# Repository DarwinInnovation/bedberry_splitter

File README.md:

# bedberry_splitter
Allows OKIN electric beds to be controlled from 2 handsets (and BedBerry v1)

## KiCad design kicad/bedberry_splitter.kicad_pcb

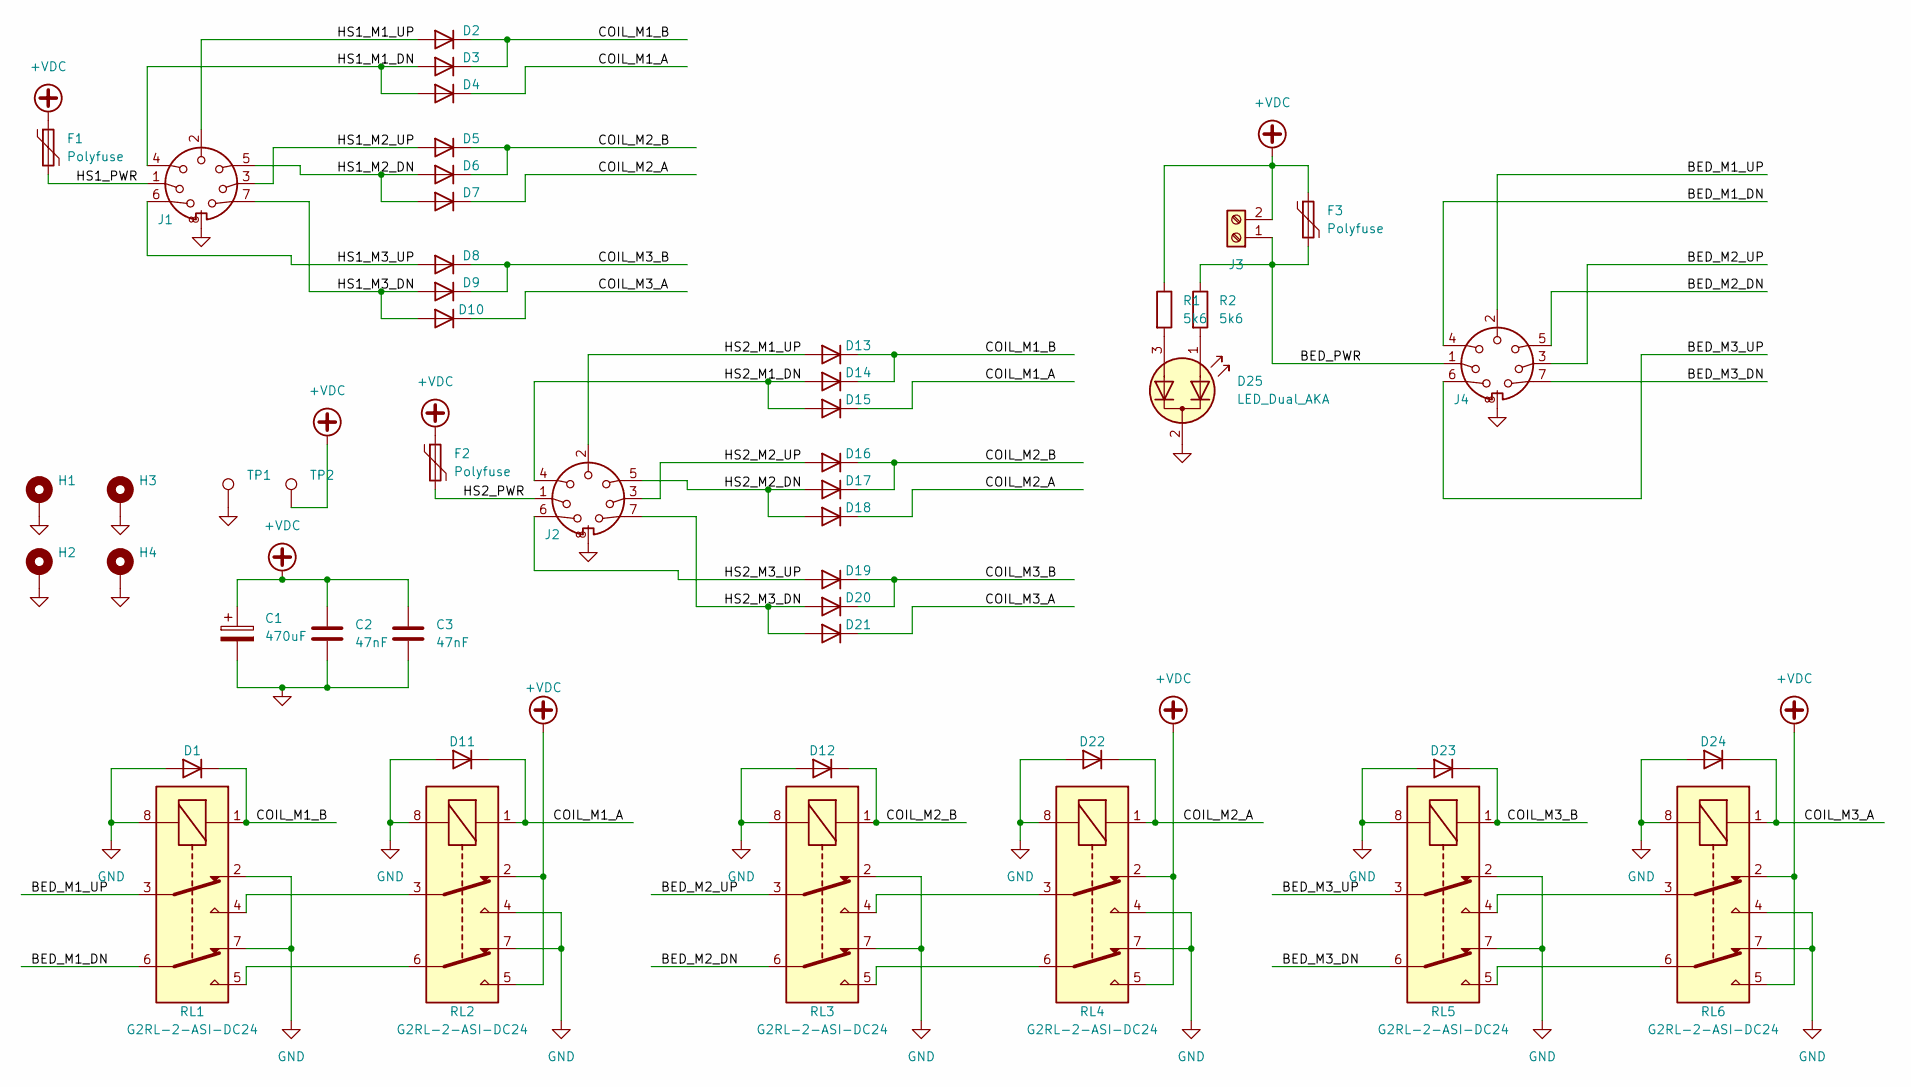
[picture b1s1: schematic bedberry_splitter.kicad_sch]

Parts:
C1: 470uF; CP_Radial_D10.0mm_P2.50mm_P5.00mm
C2, C3: 47nF; C_Disc_D7.5mm_W2.5mm_P5.00mm
D1, D2, D3, D4, D5, D6, D7, D8, D9, D10, D11, D12, D13, D14, D15, D16, D17, D18, D19, D20, D21, D22, D23, D24: 1N4002; D_DO-34_SOD68_P7.62mm_Horizontal
D25: LED_Dual_AKA; LED_D3.0mm-3
F1, F2, F3: Polyfuse; Fuse_Bourns_MF-RG300
H1, H2, H3, H4: MountingHole_Pad; MountingHole_2.7mm_M2.5_Pad
J1, J2, J4: DIN-7_with_Shield; pro-signal_DIN7_Socket
J3: Screw_Terminal_01x02; JST_NV_B02P-NV_1x02_P5.00mm_Vertical
R1, R2: 5k6; R_Axial_DIN0207_L6.3mm_D2.5mm_P2.54mm_Vertical
RL1, RL2, RL3, RL4, RL5, RL6: G2RL-2-ASI-DC24; Relay_DPDT_Omron_G2RL
TP1, TP2: TestPoint; TestPoint_Keystone_5005-5009_Compact

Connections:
+VDC: C1.1, C2.1, C3.1, F1.1, F2.1, F3.1, J3.2, R1.1, RL2.2, RL2.5, RL4.2, RL4.5, RL6.2, RL6.5, TP2.1
/BED_M1_DN: J4.4, RL1.6
/BED_M1_UP: J4.2, RL1.3
/BED_M2_DN: J4.5, RL3.6
/BED_M2_UP: J4.3, RL3.3
/BED_M3_DN: J4.7, RL5.6
/BED_M3_UP: J4.6, RL5.3
/BED_PWR: F3.2, J3.1, J4.1, R2.1
/COIL_M1_A: D4.1 (K), D11.1 (K), D15.1 (K), RL2.1
/COIL_M1_B: D1.1 (K), D2.1 (K), D3.1 (K), D13.1 (K), D14.1 (K), RL1.1
/COIL_M2_A: D7.1 (K), D18.1 (K), D22.1 (K), RL4.1
/COIL_M2_B: D5.1 (K), D6.1 (K), D12.1 (K), D16.1 (K), D17.1 (K), RL3.1
/COIL_M3_A: D10.1 (K), D21.1 (K), D24.1 (K), RL6.1
/COIL_M3_B: D8.1 (K), D9.1 (K), D19.1 (K), D20.1 (K), D23.1 (K), RL5.1
/HS1_M1_DN: D3.2 (A), D4.2 (A), J1.4
/HS1_M1_UP: D2.2 (A), J1.2
/HS1_M2_DN: D6.2 (A), D7.2 (A), J1.5
/HS1_M2_UP: D5.2 (A), J1.3
/HS1_M3_DN: D9.2 (A), D10.2 (A), J1.7
/HS1_M3_UP: D8.2 (A), J1.6
/HS1_PWR: F1.2, J1.1
/HS2_M1_DN: D14.2 (A), D15.2 (A), J2.4
/HS2_M1_UP: D13.2 (A), J2.2
/HS2_M2_DN: D17.2 (A), D18.2 (A), J2.5
/HS2_M2_UP: D16.2 (A), J2.3
/HS2_M3_DN: D20.2 (A), D21.2 (A), J2.7
/HS2_M3_UP: D19.2 (A), J2.6
/HS2_PWR: F2.2, J2.1
GND: C1.2, C2.2, C3.2, D1.2 (A), D11.2 (A), D12.2 (A), D22.2 (A), D23.2 (A), D24.2 (A), D25.2 (K), H1.1, H2.1, H3.1, H4.1, J1.8, J2.8, J4.8, RL1.2, RL1.7, RL1.8, RL2.4, RL2.7, RL2.8, RL3.2, RL3.7, RL3.8, RL4.4, RL4.7, RL4.8, RL5.2, RL5.7, RL5.8, RL6.4, RL6.7, RL6.8, TP1.1; also elsewhere on the board
unnamed: D25.1 (A1), R2.2
unnamed: D25.3 (A2), R1.2
unnamed: RL1.4, RL2.3
unnamed: RL1.5, RL2.6
unnamed: RL3.4, RL4.3
unnamed: RL3.5, RL4.6
unnamed: RL5.4, RL6.3
unnamed: RL5.5, RL6.6

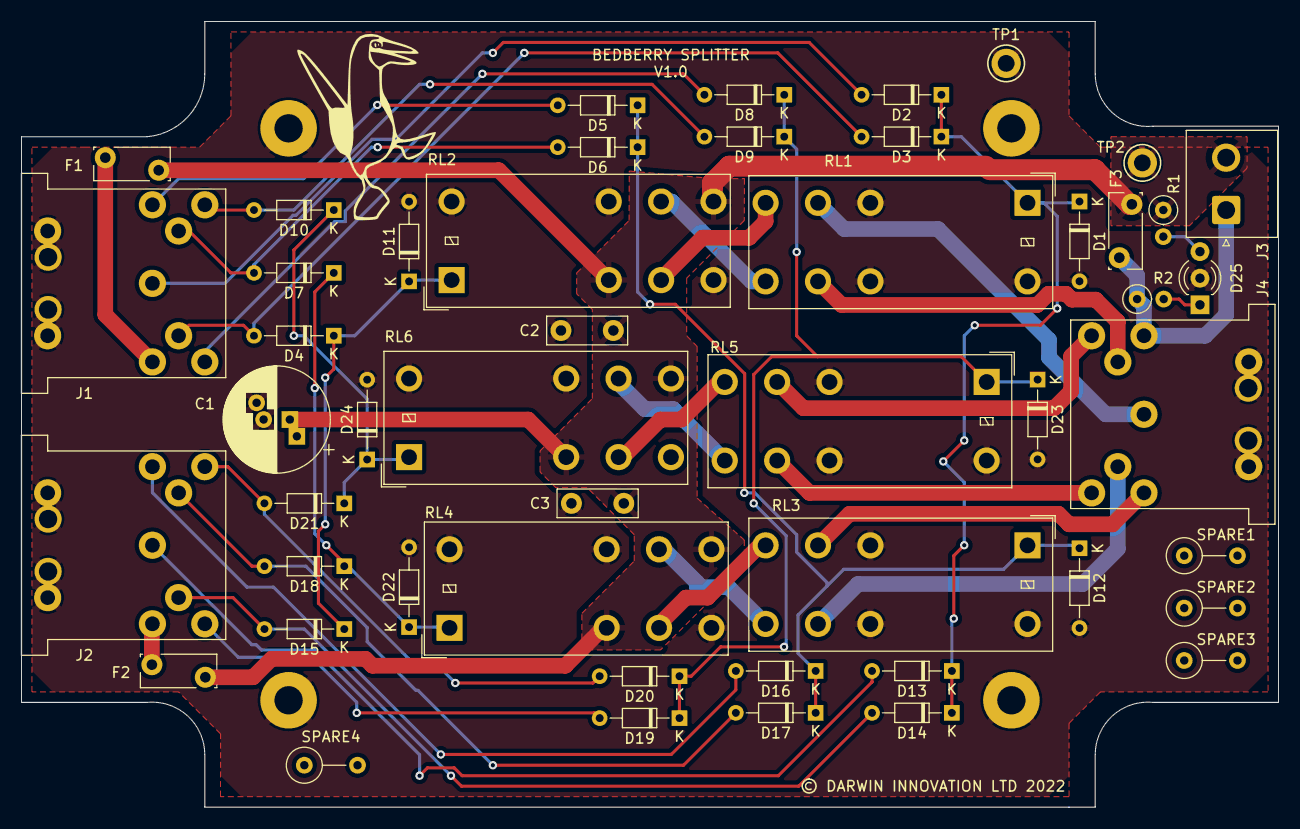
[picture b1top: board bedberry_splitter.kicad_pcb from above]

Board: 2 copper layers, 120.0 x 75.0 mm, 53 parts (0 on the bottom side), 37 nets.

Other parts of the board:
SPARE1, SPARE2, SPARE3, SPARE4: R_Axial_DIN0309_L9.0mm_D3.2mm_P5.08mm_Vertical
locked: MountingHole_Pad; MountingHole_2.7mm_M2.5_Pad
locked#2: locked; MountingHole_2.7mm_M2.5_Pad
locked#3: MountingHole_Pad; MountingHole_2.7mm_M2.5_Pad

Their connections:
GND: locked.1, locked#2.1, locked#3.1; also elsewhere on the board

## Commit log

2023-01-23 add kicad files
2023-01-23 add gerbers & drill file
2023-01-23 Add schematic and images

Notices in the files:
kicad/bedberry_splitter.kicad_pcb:
© DARWIN INNOVATION LTD 2022
